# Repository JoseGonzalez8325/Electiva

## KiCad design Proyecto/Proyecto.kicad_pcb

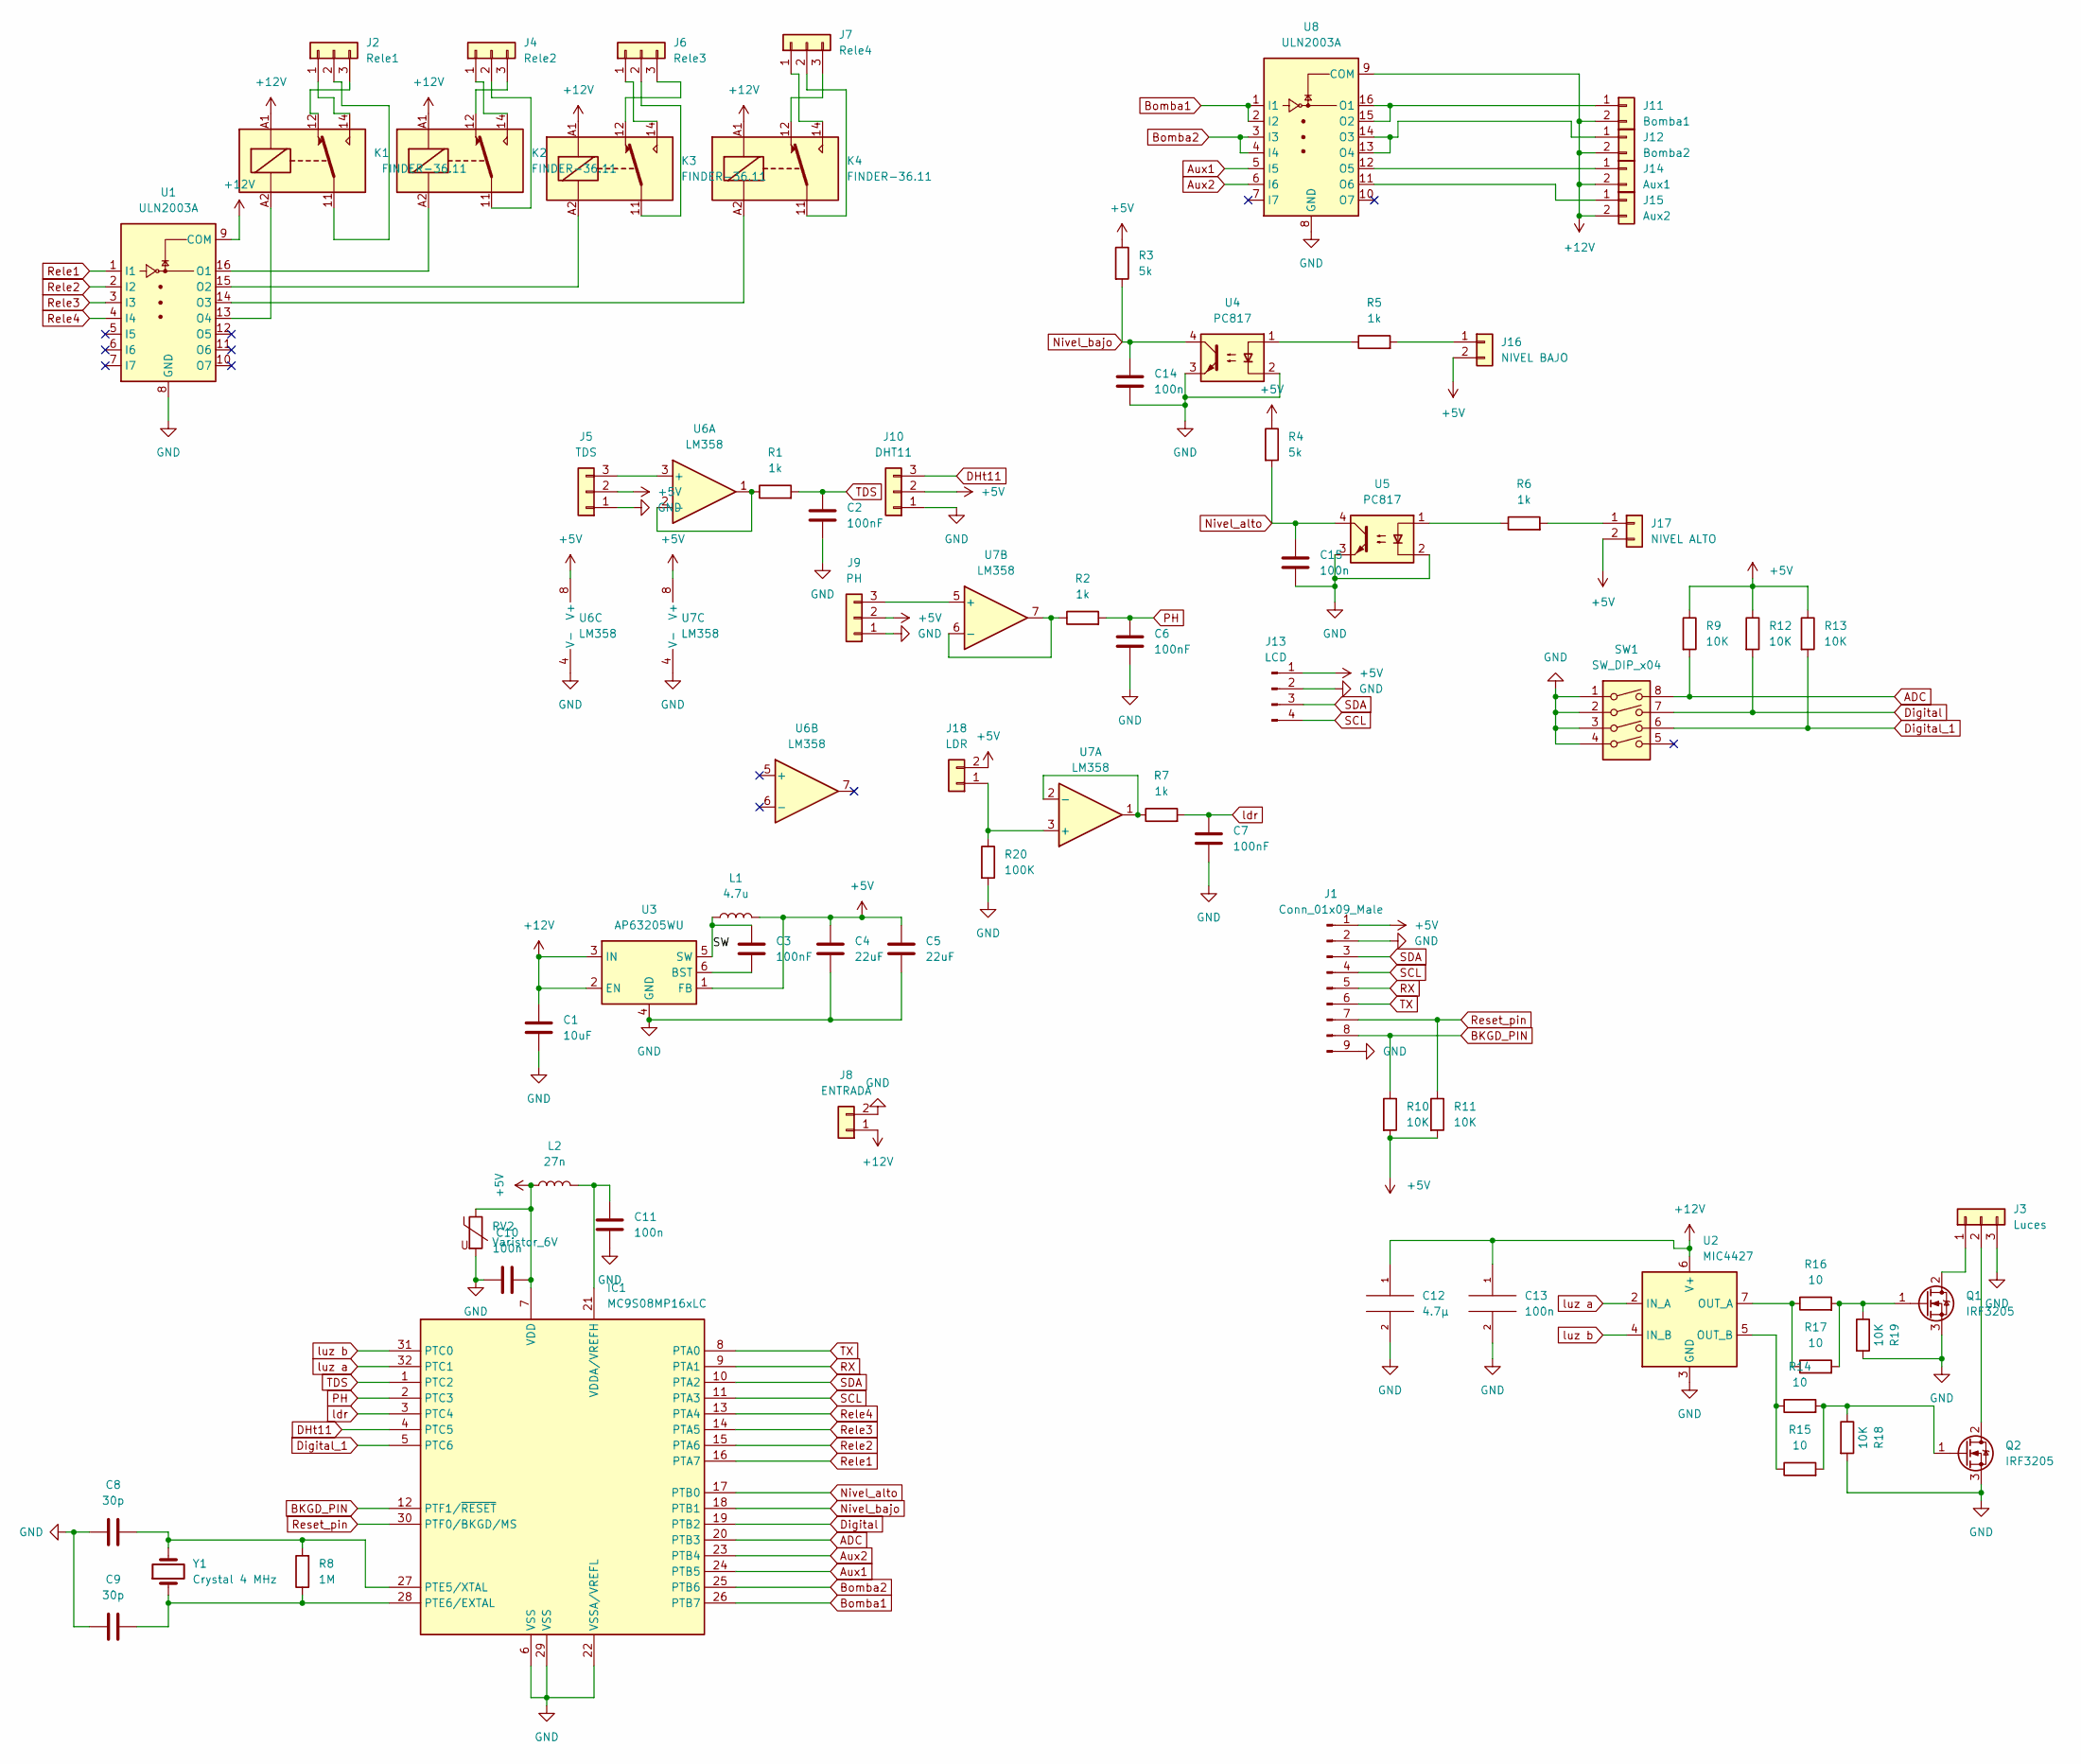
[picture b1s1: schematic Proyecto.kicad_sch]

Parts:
C1: 10uF; C_0805_2012Metric
C2, C6, C7: 100nF; C_0603_1608Metric
C3: 100nF; C_0201_0603Metric
C4, C5: 22uF; C_0805_2012Metric
C8, C9: 30p; C_0201_0603Metric
C10, C11, C13, C14, C15: 100n; C_0201_0603Metric
C12: 4.7µ; C_0805_2012Metric
IC1: MC9S08MP16xLC; LQFP-32_7x7mm_P0.8mm
J1: Conn_01x09_Male; PinHeader_1x09_P2.54mm_Vertical
J2: Rele1; TerminalBlock_bornier-3_P5.08mm
J3: Luces; TerminalBlock_bornier-3_P5.08mm
J4: Rele2; TerminalBlock_bornier-3_P5.08mm
J5: TDS; TerminalBlock_bornier-3_P5.08mm
J6: Rele3; TerminalBlock_bornier-3_P5.08mm
J7: Rele4; TerminalBlock_bornier-3_P5.08mm
J8: ENTRADA; TerminalBlock_bornier-2_P5.08mm
J9: PH; TerminalBlock_bornier-3_P5.08mm
J10: DHT11; TerminalBlock_bornier-3_P5.08mm
J11: Bomba1; TerminalBlock_bornier-2_P5.08mm
J12: Bomba2; TerminalBlock_bornier-2_P5.08mm
J13: LCD; PinHeader_1x04_P2.54mm_Vertical
J14: Aux1; TerminalBlock_bornier-2_P5.08mm
J15: Aux2; TerminalBlock_bornier-2_P5.08mm
J16: NIVEL BAJO; TerminalBlock_bornier-2_P5.08mm
J17: NIVEL ALTO; TerminalBlock_bornier-2_P5.08mm
J18: LDR; TerminalBlock_bornier-2_P5.08mm
K1, K2, K3, K4: FINDER-36.11; Relay_SPDT_Finder_36.11
L1: 4.7u; L_Bourns_SRN6045TA
L2: 27n; L_0805_2012Metric
Q1, Q2: IRF3205; TO-220-3_Vertical
R1, R2, R5, R6, R7: 1k; R_0603_1608Metric
R3, R4: 5k; R_0603_1608Metric
R8: 1M; R_0201_0603Metric
R9, R10, R11, R12, R13, R18, R19: 10K; R_0201_0603Metric
R14, R15, R16, R17: 10; R_0201_0603Metric
R20: 100K; R_0201_0603Metric
RV2: Varistor_6V; C_0805_2012Metric
SW1: SW_DIP_x04; SW_DIP_SPSTx04_Slide_9.78x12.34mm_W8.61mm_P2.54mm
U1, U8: ULN2003A; SOIC-16_3.9x9.9mm_P1.27mm
U2: MIC4427; SOIC-8_3.9x4.9mm_P1.27mm
U3: AP63205WU; TSOT-23-6
U4, U5: PC817; DIP-4_W7.62mm
U6, U7: LM358; SOIC-8_3.9x4.9mm_P1.27mm
Y1: Crystal 4 MHz; Crystal_HC49-4H_Vertical

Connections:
+5V: C4.1, C5.1, C10.2, IC1.7 (VDD), J1.1, J5.2, J9.2, J10.2, J13.1, J16.2, J17.2, J18.2, L1.2, L2.1, R3.1, R4.1, R9.1, R10.2, R11.2, R12.1, R13.1, RV2.1, U3.1 (FB), U6.8 (V+), U7.8 (V+)
+12V: C1.1, C12.1, C13.1, J8.1, J11.2, J12.2, J14.2, J15.2, K1.A1, K2.A1, K3.A1, K4.A1, U1.9 (COM), U2.6 (V+), U3.2 (EN), U3.3 (IN), U8.9 (COM)
/SW: C3.1, L1.1, U3.5 (SW)
ADC: IC1.20 (PTB3), R9.2, SW1.8
Aux1: IC1.24 (PTB5), U8.5 (I5)
Aux2: IC1.23 (PTB4), U8.6 (I6)
BKGD_PIN: IC1.12 (PTF1/~RESET), J1.8, R10.1
Bomba1: IC1.26 (PTB7), U8.1 (I1), U8.2 (I2)
Bomba2: IC1.25 (PTB6), U8.3 (I3), U8.4 (I4)
DHt11: IC1.4 (PTC5), J10.3
Digital: IC1.19 (PTB2), R12.2, SW1.7
Digital_1: IC1.5 (PTC6), R13.2, SW1.6
GND: C1.2, C2.2, C4.2, C5.2, C6.2, C7.2, C8.1, C9.1, C10.1, C11.1, C12.2, C13.2, C14.2, C15.2, IC1.6 (VSS), IC1.22 (VSSA/VREFL), IC1.29 (VSS), J1.2, J1.9, J3.3, J5.1, J8.2, J9.1, J10.1, J13.2, Q1.3 (S), Q2.3 (S), R18.2, R19.2, R20.2, RV2.2, SW1.1, SW1.2, SW1.3, SW1.4, U1.8 (GND), U2.3 (GND), U3.4 (GND), U4.2, U4.3, U5.2, U5.3, U6.4 (V-), U7.4 (V-), U8.8 (GND)
unnamed: C3.2, U3.6 (BST)
unnamed: C8.2, IC1.27 (PTE5/XTAL), R8.2, Y1.2
unnamed: C9.2, IC1.28 (PTE6/EXTAL), R8.1, Y1.1
unnamed: C11.2, IC1.21 (VDDA/VREFH), L2.2
unnamed: J2.1, K1.14
unnamed: J2.2, K1.11
unnamed: J2.3, K1.12
unnamed: J3.1, Q1.2 (D)
unnamed: J3.2, Q2.2 (D)
unnamed: J4.1, K2.14
unnamed: J4.2, K2.11
unnamed: J4.3, K2.12
unnamed: J5.3, U6.3 (+)
unnamed: J6.1, K3.14
unnamed: J6.2, K3.11
unnamed: J6.3, K3.12
unnamed: J7.1, K4.14
unnamed: J7.2, K4.11
unnamed: J7.3, K4.12
unnamed: J9.3, U7.5 (+)
unnamed: J11.1, U8.15 (O2), U8.16 (O1)
unnamed: J12.1, U8.13 (O4), U8.14 (O3)
unnamed: J14.1, U8.12 (O5)
unnamed: J15.1, U8.11 (O6)
unnamed: J16.1, R5.2
unnamed: J17.1, R6.2
unnamed: J18.1, R20.1, U7.3 (+)
unnamed: K1.A2, U1.13 (O4)
unnamed: K2.A2, U1.16 (O1)
unnamed: K3.A2, U1.15 (O2)
unnamed: K4.A2, U1.14 (O3)
unnamed: Q1.1 (G), R16.2, R17.2, R19.1
unnamed: Q2.1 (G), R14.2, R15.2, R18.1
unnamed: R1.1, U6.1, U6.2 (-)
unnamed: R2.1, U7.6 (-), U7.7
unnamed: R5.1, U4.1
unnamed: R6.1, U5.1
unnamed: R7.1, U7.1, U7.2 (-)
unnamed: R14.1, R15.1, U2.5 (OUT_B)
unnamed: R16.1, R17.1, U2.7 (OUT_A)
Nivel_alto: C15.1, IC1.17 (PTB0), R4.2, U5.4
Nivel_bajo: C14.1, IC1.18 (PTB1), R3.2, U4.4
PH: C6.1, IC1.2 (PTC3), R2.2
RX: IC1.9 (PTA1), J1.5
Rele1: IC1.16 (PTA7), U1.1 (I1)
Rele2: IC1.15 (PTA6), U1.2 (I2)
Rele3: IC1.14 (PTA5), U1.3 (I3)
Rele4: IC1.13 (PTA4), U1.4 (I4)
Reset_pin: IC1.30 (PTF0/BKGD/MS), J1.7, R11.1
SCL: IC1.11 (PTA3), J1.4, J13.4
SDA: IC1.10 (PTA2), J1.3, J13.3
TDS: C2.1, IC1.1 (PTC2), R1.2
TX: IC1.8 (PTA0), J1.6
ldr: C7.1, IC1.3 (PTC4), R7.2
luz a: IC1.32 (PTC1), U2.2 (IN_A)
luz b: IC1.31 (PTC0), U2.4 (IN_B)

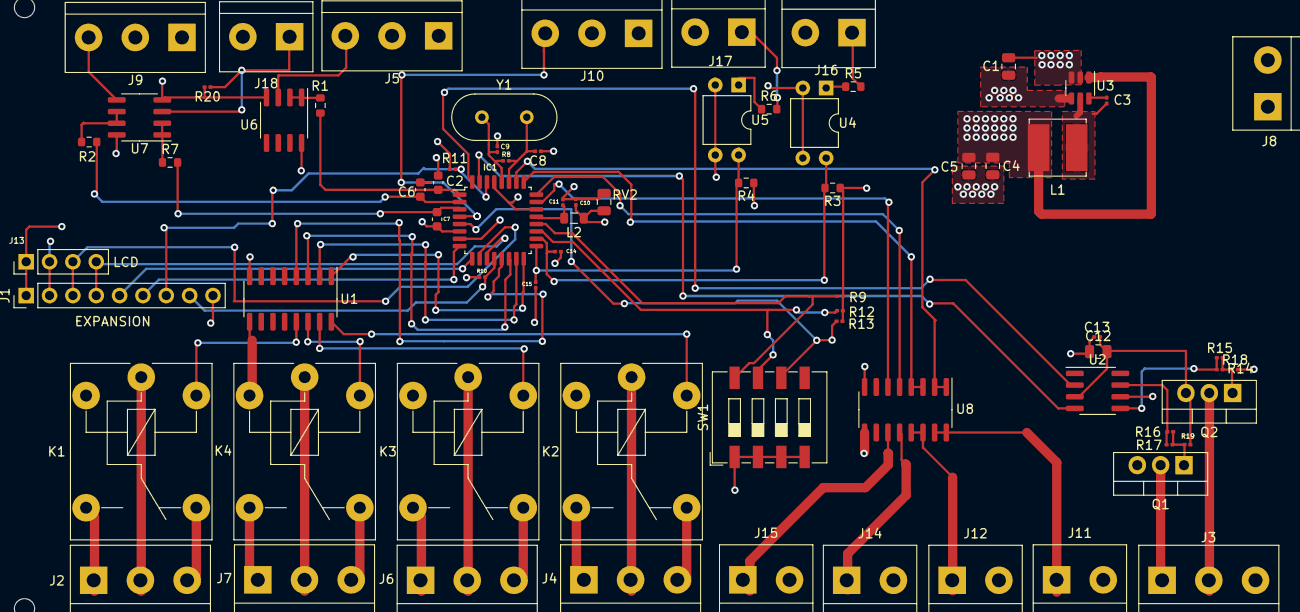
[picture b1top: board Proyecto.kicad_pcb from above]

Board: 4 copper layers, 77 parts (0 on the bottom side), 69 nets.

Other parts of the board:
HOLE3, HOLE3#2, HOLE3#3, HOLE3#4: MountingHole_2.2mm_M2

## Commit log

2022-06-03 Soy el boss
2022-06-10 Tarea
2022-06-10 Logo
2022-06-10 Informes
2022-06-24 Proyecto
2022-07-01 30-6-2022
2022-07-01 1-7-2022
2022-07-01 7-1-2022
2022-07-08 7-8-2022 itLA
2022-07-15 15-7-2022
2022-07-15 7-15-2022 ITLA
2022-07-22 22-7-2022
